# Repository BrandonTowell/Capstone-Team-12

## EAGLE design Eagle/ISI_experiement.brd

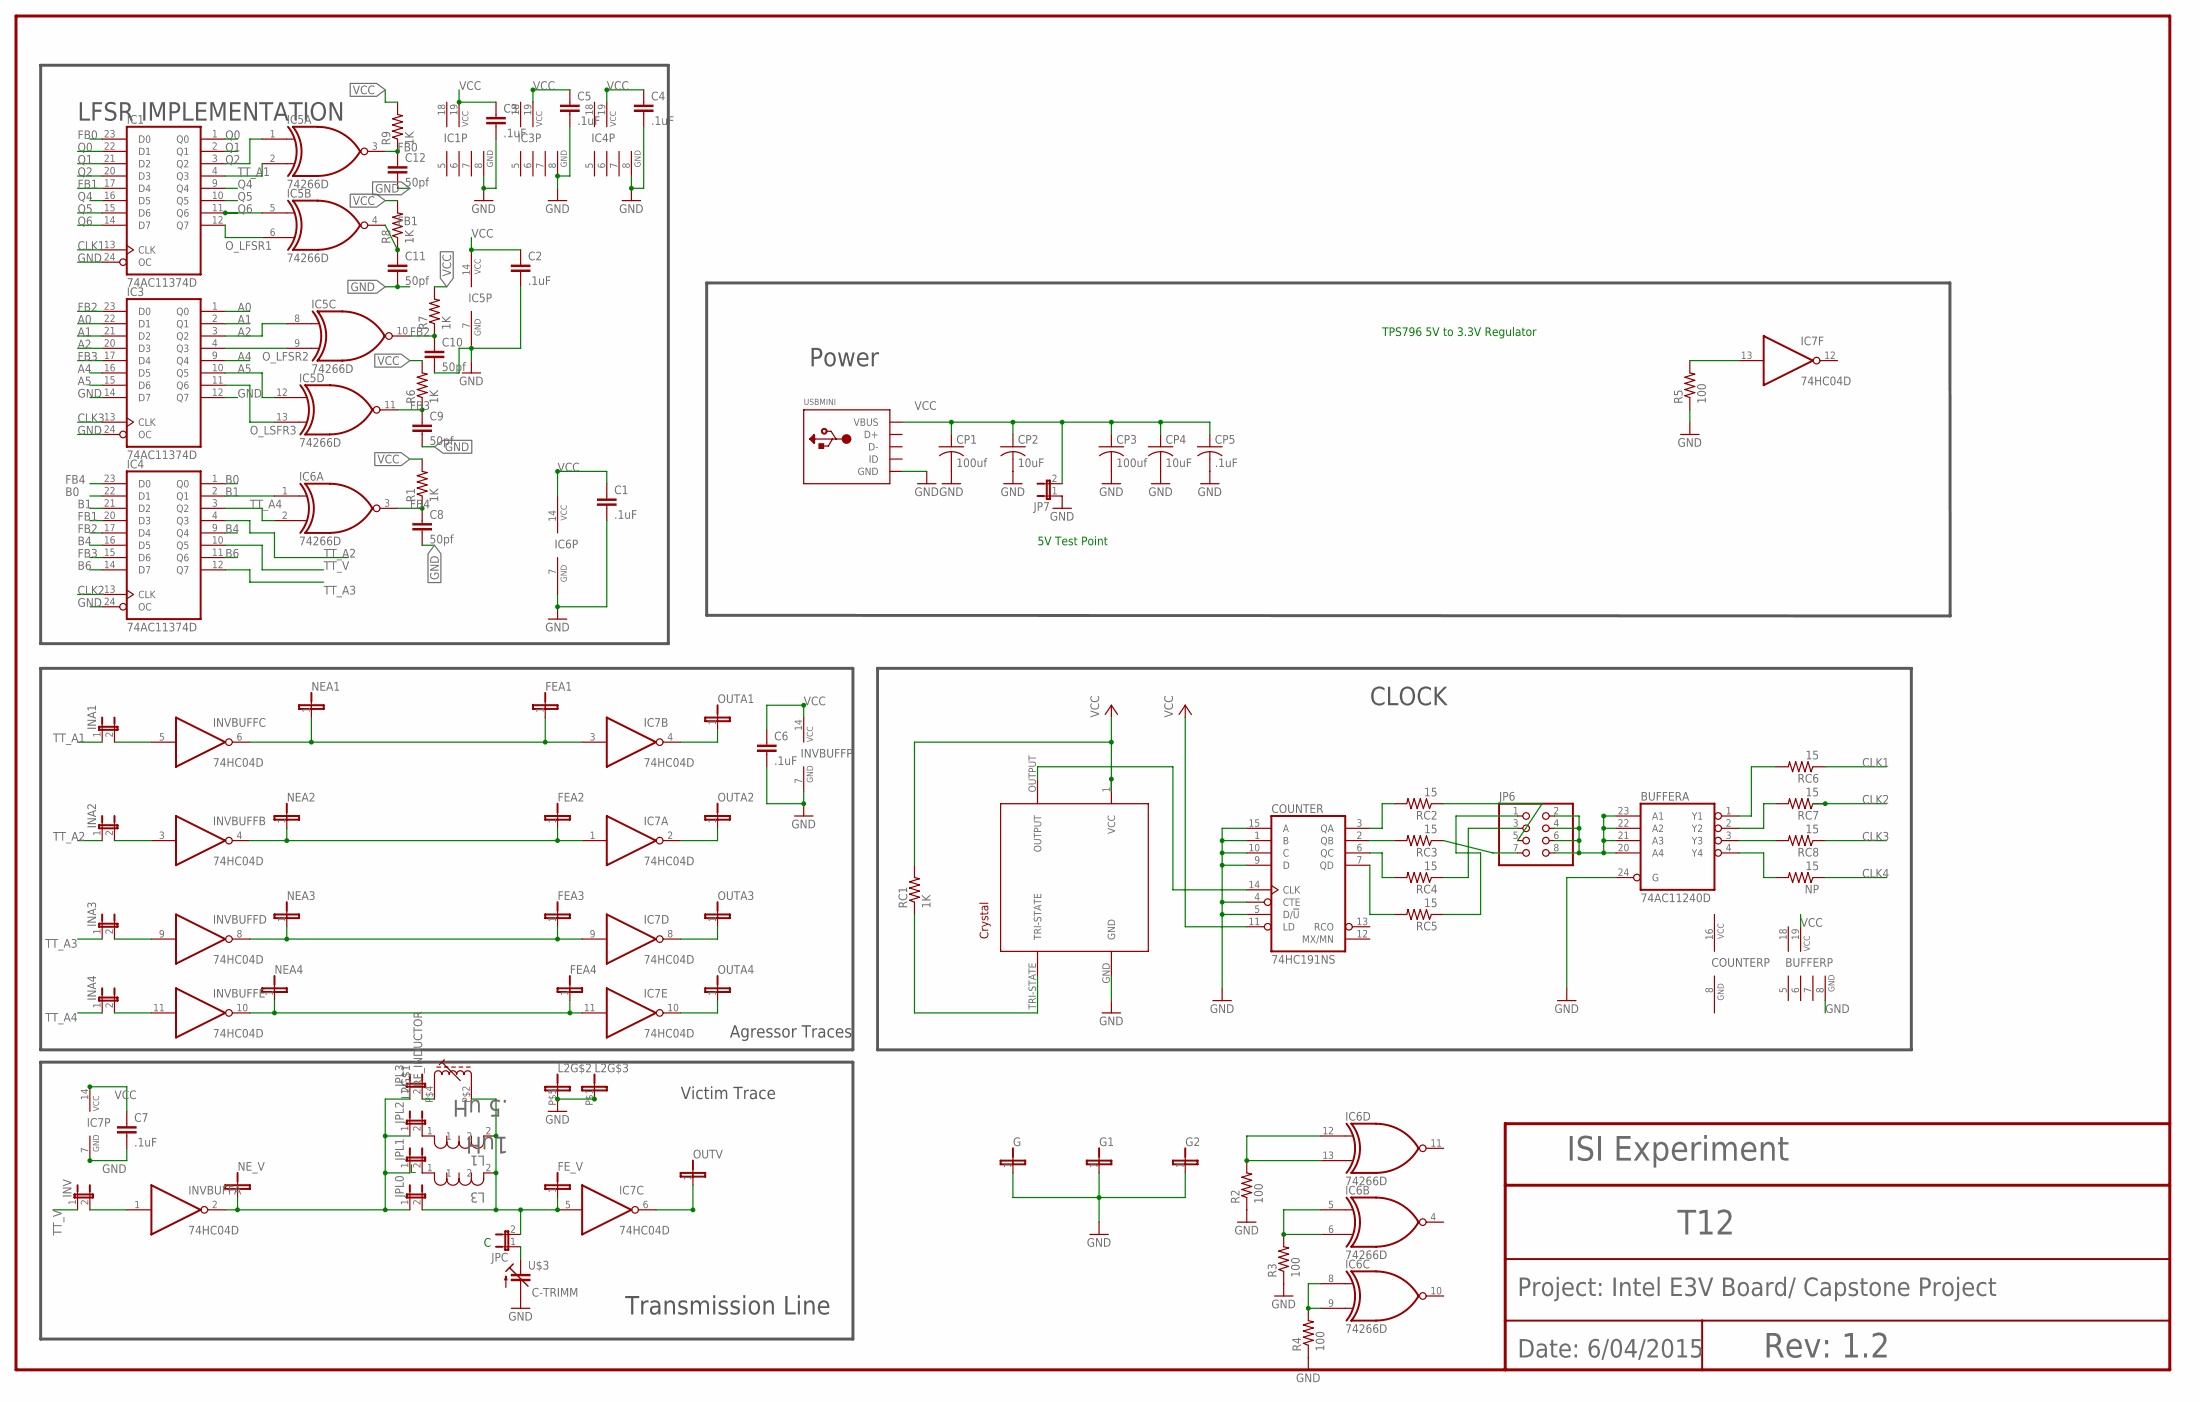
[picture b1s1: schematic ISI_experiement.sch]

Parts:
BUFFER: 74AC11240D; SO24W
C1, C2, C3, C4, C5, C6, C7: .1uF; C0805
C8, C9, C10, C11, C12: 50pf; C0805
COUNTER: 74HC191NS; SO16NS
CP1, CP3: 100uf; C1206K
CP2, CP4: 10uF; C1206K
CP5: .1uF; C1206K
FEA1, FEA2, FEA3, FEA4: JP1
FE_V: JP1
G, G1, G2: JP1
IC1, IC3, IC4: 74AC11374D; SO24W
IC5, IC6: 74266D; SO14
IC7: 74HC04D; SO14
INA1, INA2, INA3, INA4: JP1E; JP1
INV: JP1E; JP1
INVBUFF: 74HC04D; SO14
JP6: PINHD-2X4; 2X04
JP7: JP1E; JP1
JPC: JP1E; JP1
JPL0, JPL1, JPL2, JPL3: JP1E; JP1
L1: .5 uH; INDC2115X15N
L2: RF_INDUCTOR; ADJ_IND_NON_STD_PKG
L3: 1uH; INDC2115X15N
NEA1, NEA2, NEA3, NEA4: JP1
NE_V: JP1
NP: 15; R0805
OUTA1, OUTA2, OUTA3, OUTA4: JP1
OUTV: JP1
R1, R6, R7, R8, R9: 1K; M0805
R2, R3, R4, R5: 100; M0805
RC1: 1K; R0805
RC2, RC3, RC4, RC5, RC6, RC7, RC8: 15; R0805
U$1: ECS-8FX
U$3: C-TRIMM; C_TRIM
USBMINI: USBMINIB; USB-MINIB

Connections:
1: FEA1.1, IC7.3 (I), INVBUFF.6 (O), NEA1.1
2: FEA2.1, IC7.1 (I), INVBUFF.4 (O), NEA2.1
3: FEA3.1, IC7.9 (I), INVBUFF.8 (O), NEA3.1
8: FEA4.1, IC7.11 (I), INVBUFF.10 (O), NEA4.1
A0: IC3.1 (Q0), IC3.22 (D1)
A1: IC3.2 (Q1), IC3.21 (D2)
A2: IC3.3 (Q2), IC3.20 (D3), IC5.8 (I0)
A4: IC3.9 (Q4), IC3.16 (D5)
A5: IC3.10 (Q5), IC3.15 (D6), IC5.12 (I0)
B0: IC4.1 (Q0), IC4.22 (D1)
B1: IC4.2 (Q1), IC4.21 (D2), IC6.1 (I0)
B4: IC4.9 (Q4), IC4.16 (D5)
B6: IC4.11 (Q6), IC4.14 (D7)
CLK1: IC1.13 (CLK), RC6.1
CLK2: IC4.13 (CLK), RC7.1
CLK3: IC3.13 (CLK), RC8.1
CLK4: NP.1
CRY_OUT: COUNTER.14 (CLK), U$1.OUTPUT
FB0: C12.1, IC1.23 (D0), IC5.3 (O), R9.1
FB1: C11.1, IC1.17 (D4), IC4.20 (D3), IC5.4 (O), R8.1
FB2: C10.1, IC3.23 (D0), IC4.17 (D4), IC5.10 (O), R7.1
FB3: C9.1, IC3.17 (D4), IC4.15 (D6), IC5.11 (O), R6.1
FB4: C8.1, IC4.23 (D0), IC6.3 (O), R1.1
GND: BUFFER.5 (GND), BUFFER.6 (GND), BUFFER.7 (GND), BUFFER.8 (GND), BUFFER.24 (G), C1.2, C2.2, C3.2, C4.2, C5.2, C6.2, C7.2, C8.2, C9.2, C10.2, C11.2, C12.2, COUNTER.1 (B), COUNTER.4 (CTE), COUNTER.5 (D/!U), COUNTER.8 (GND), COUNTER.9 (D), COUNTER.10 (C), COUNTER.15 (A), CP1.2, CP2.2, CP3.2, CP4.2, CP5.2, G.1, G1.1, G2.1, IC1.5 (GND), IC1.6 (GND), IC1.7 (GND), IC1.8 (GND), IC1.24 (OC), IC3.5 (GND), IC3.6 (GND), IC3.7 (GND), IC3.8 (GND), IC3.12 (Q7), IC3.14 (D7), IC3.24 (OC), IC4.5 (GND), IC4.6 (GND), IC4.7 (GND), IC4.8 (GND), IC4.24 (OC), IC5.7 (GND), IC6.7 (GND), IC7.7 (GND), INVBUFF.7 (GND), JP7.1, L2.P$1 (1), L2.P$5 (1), R2.1, R3.1, R4.1, R5.1, U$1.GND, U$3.- (G), USBMINI.GND
unnamed: INA2.2, INVBUFF.3 (I)
unnamed: JPL3.2, L2.P$4 (A1)
unnamed: FE_V.1, IC7.5 (I), JPC.2, JPL0.2, L1.2, L2.P$2 (E1), L3.2
unnamed: RC1.1, U$1.TRI-STATE
unnamed: COUNTER.7 (QD), RC5.2
unnamed: JPC.1, U$3.+
unnamed: IC7.4 (O), OUTA1.1
unnamed: INA1.2, INVBUFF.5 (I)
unnamed: COUNTER.3 (QA), RC2.2
unnamed: IC6.12 (I0), IC6.13 (I1), R2.2
unnamed: IC7.6 (O), OUTV.1
unnamed: JPL2.2, L1.1
unnamed: IC7.10 (O), OUTA4.1
unnamed: IC7.2 (O), OUTA2.1
unnamed: INA4.2, INVBUFF.11 (I)
unnamed: INV.2, INVBUFF.1 (I)
unnamed: COUNTER.2 (QB), RC3.2
unnamed: JPL1.2, L3.1
unnamed: INA3.2, INVBUFF.9 (I)
unnamed: COUNTER.6 (QC), RC4.2
unnamed: IC6.5 (I0), IC6.6 (I1), R3.2
unnamed: JP6.5, RC2.1
unnamed: JP6.3, RC4.1
unnamed: JP6.7, RC3.1
unnamed: JP6.1, RC5.1
unnamed: BUFFER.20 (A4), BUFFER.21 (A3), BUFFER.22 (A2), BUFFER.23 (A1), JP6.2, JP6.4, JP6.6, JP6.8
unnamed: BUFFER.1 (Y1), RC6.2
unnamed: BUFFER.2 (Y2), RC7.2
unnamed: BUFFER.3 (Y3), RC8.2
unnamed: BUFFER.4 (Y4), NP.2
unnamed: IC6.8 (I0), IC6.9 (I1), R4.2
unnamed: IC7.13 (I), R5.2
OUTA4: IC7.8 (O), OUTA3.1
O_LFSR1: IC1.12 (Q7), IC5.6 (I1)
O_LFSR2: IC3.4 (Q3), IC5.9 (I1)
O_LSFR3: IC3.11 (Q6), IC5.13 (I1)
Q0: IC1.1 (Q0), IC1.22 (D1)
Q1: IC1.2 (Q1), IC1.21 (D2)
Q2: IC1.3 (Q2), IC1.20 (D3), IC5.1 (I0)
Q4: IC1.9 (Q4), IC1.16 (D5)
Q5: IC1.10 (Q5), IC1.15 (D6)
Q6: IC1.11 (Q6), IC1.14 (D7), IC5.5 (I0)
TT_A1: IC1.4 (Q3), IC5.2 (I1), INA1.1
TT_A2: IC4.4 (Q3), INA2.1
TT_A3: IC4.12 (Q7), INA3.1
TT_A4: IC4.3 (Q2), IC6.2 (I1), INA4.1
TT_V: IC4.10 (Q5), INV.1
V1: INVBUFF.2 (O), JPL0.1, JPL1.1, JPL2.1, JPL3.1, NE_V.1
VCC: BUFFER.18 (VCC), BUFFER.19 (VCC), C1.1, C2.1, C3.1, C4.1, C5.1, C6.1, C7.1, COUNTER.11 (LD), COUNTER.16 (VCC), CP1.1, CP2.1, CP3.1, CP4.1, CP5.1, IC1.18 (VCC), IC1.19 (VCC), IC3.18 (VCC), IC3.19 (VCC), IC4.18 (VCC), IC4.19 (VCC), IC5.14 (VCC), IC6.14 (VCC), IC7.14 (VCC), INVBUFF.14 (VCC), JP7.2, R1.2, R6.2, R7.2, R8.2, R9.2, RC1.2, U$1.1 (VCC), USBMINI.VBUS

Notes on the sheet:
LFSR IMPLEMENTATION
Transmission Line
Power
CLOCK
ISI Experiment
T12
Rev: 1.2
Date: 6/04/2015
Project: Intel E3V Board/ Capstone Project
TPS796 5V to 3.3V Regulator
5V Test Point
Victim Trace
Agressor Traces

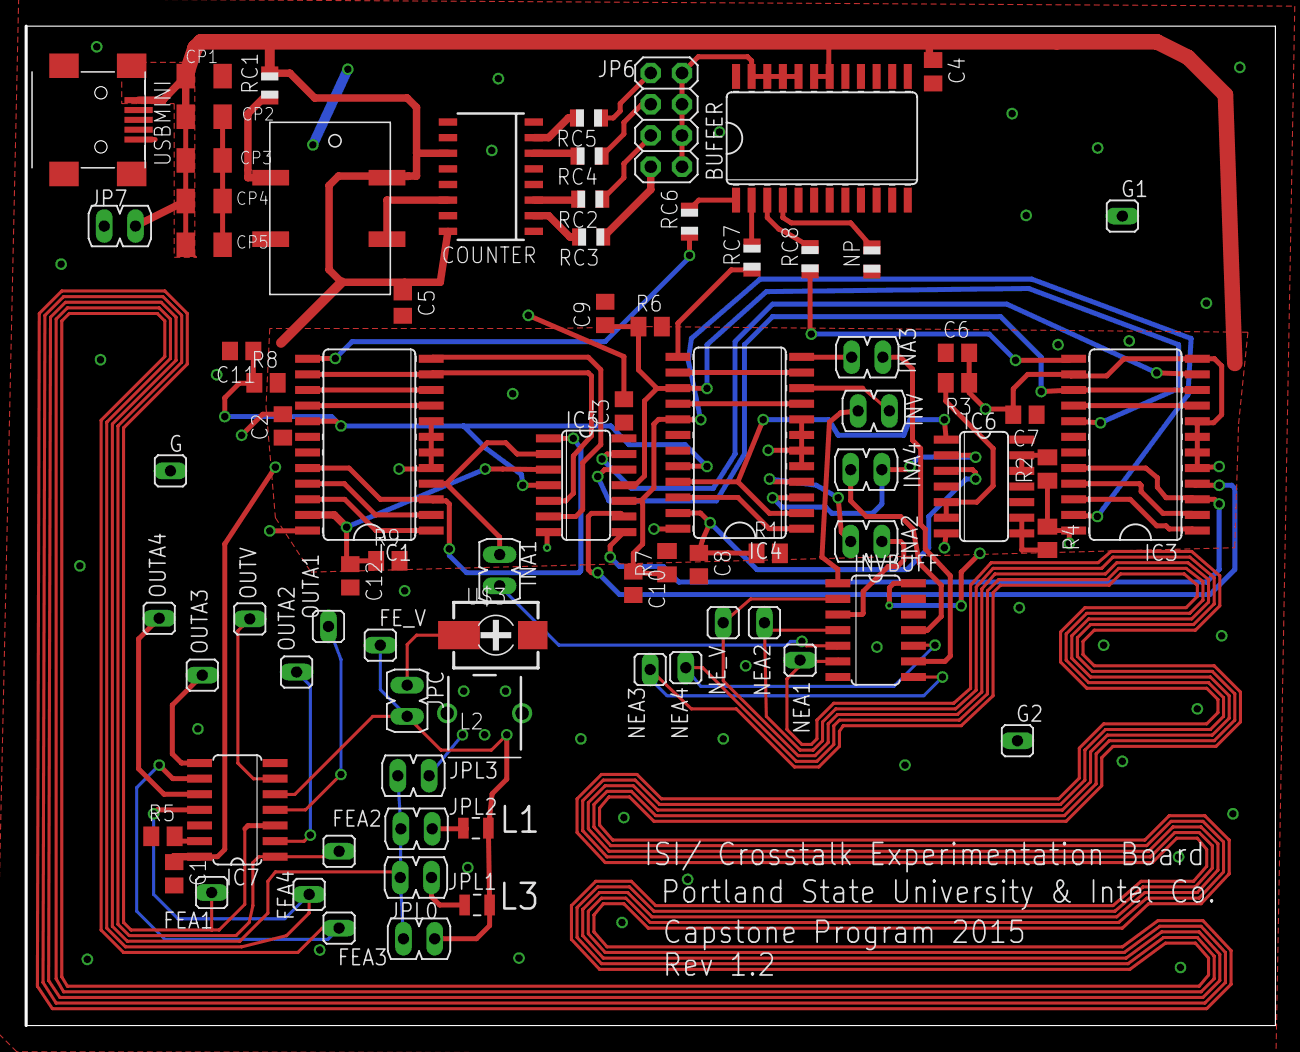
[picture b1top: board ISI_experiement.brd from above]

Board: 2 copper layers, 101.6 x 81.3 mm, 80 parts (0 on the bottom side), 72 nets.

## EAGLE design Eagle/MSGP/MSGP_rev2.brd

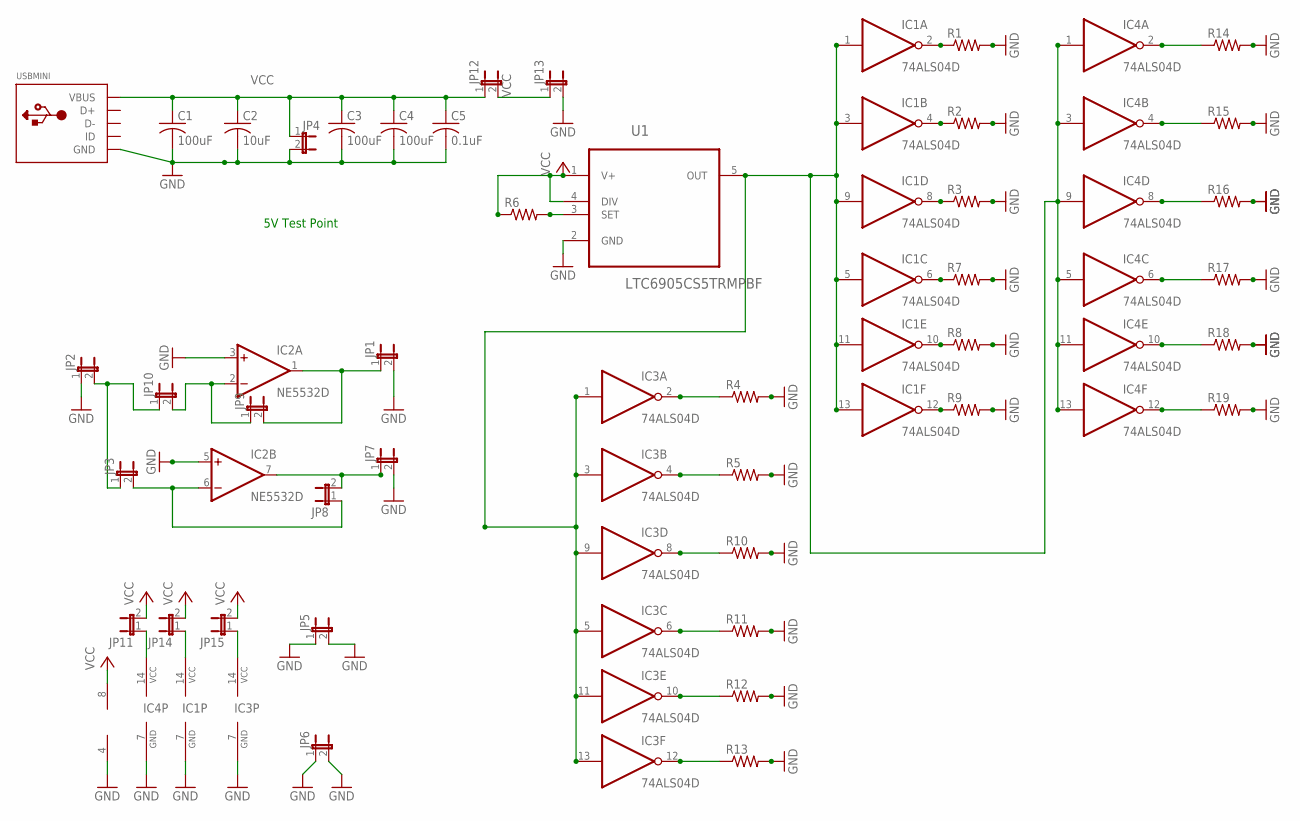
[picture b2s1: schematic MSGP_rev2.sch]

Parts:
C1, C3, C4: 100uF; C1206K
C2: 10uF; C1206K
C5: 0.1uF; C1206K
IC1, IC3, IC4: 74ALS04D; SO14
IC2: NE5532D; SO08
JP1, JP2, JP3, JP4, JP5, JP6, JP7, JP8, JP9, JP10, JP11, JP12, JP13, JP14, JP15: JP1E; JP1
R1, R2, R3, R4, R5, R6, R7, R8, R9, R10, R11, R12, R13, R14, R15, R16, R17, R18, R19: R-US_0204/2V; 0204V
U1: LTC6905CS5TRMPBF; SOT95P280X100-5N
USBMINI: USBMINIB; USB-MINIB

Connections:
GNDA: C1.2, C2.2, C3.2, C4.2, C5.2, IC2.3 (+IN), IC2.4 (V-), IC2.5 (+IN), JP1.2, JP2.1, JP4.2, JP5.2, JP6.2, JP7.2, JP13.2, USBMINI.GND
GND_D: IC1.7 (GND), IC3.7 (GND), IC4.7 (GND), JP5.1, JP6.1, R1.2, R2.2, R3.2, R4.2, R5.2, R7.2, R8.2, R9.2, R10.2, R11.2, R12.2, R13.2, R14.2, R15.2, R16.2, R17.2, R18.2, R19.2, U1.2 (GND)
unnamed: IC1.1 (I), IC1.3 (I), IC1.5 (I), IC1.9 (I), IC1.11 (I), IC1.13 (I), IC3.1 (I), IC3.3 (I), IC3.5 (I), IC3.9 (I), IC3.11 (I), IC3.13 (I), IC4.1 (I), IC4.3 (I), IC4.5 (I), IC4.9 (I), IC4.11 (I), IC4.13 (I), U1.5 (OUT)
unnamed: IC2.6 (-IN), JP3.2, JP8.1
unnamed: IC2.1 (OUT), JP1.1, JP9.2
unnamed: IC1.10 (O), R8.1
unnamed: IC2.2 (-IN), JP9.1, JP10.2
unnamed: R6.2, U1.3 (SET)
unnamed: IC1.2 (O), R1.1
unnamed: IC1.4 (O), R2.1
unnamed: IC1.8 (O), R3.1
unnamed: IC1.6 (O), R7.1
unnamed: IC1.12 (O), R9.1
unnamed: IC2.7 (OUT), JP7.1, JP8.2
unnamed: IC3.10 (O), R12.1
unnamed: IC4.14 (VCC), JP11.1
unnamed: IC3.2 (O), R4.1
unnamed: IC3.4 (O), R5.1
unnamed: IC3.8 (O), R10.1
unnamed: IC3.6 (O), R11.1
unnamed: IC3.12 (O), R13.1
unnamed: IC4.10 (O), R18.1
unnamed: IC1.14 (VCC), JP14.1
unnamed: IC4.2 (O), R14.1
unnamed: IC4.4 (O), R15.1
unnamed: IC4.8 (O), R16.1
unnamed: IC4.6 (O), R17.1
unnamed: IC4.12 (O), R19.1
unnamed: IC3.14 (VCC), JP15.1
unnamed: JP2.2, JP3.1, JP10.1
VCC: C1.1, C2.1, C3.1, C4.1, C5.1, IC2.8 (V+), JP4.1, JP11.2, JP12.1, JP12.2, JP13.1, JP14.2, JP15.2, R6.1, U1.1 (V+), U1.4 (DIV), USBMINI.VBUS

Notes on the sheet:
5V Test Point

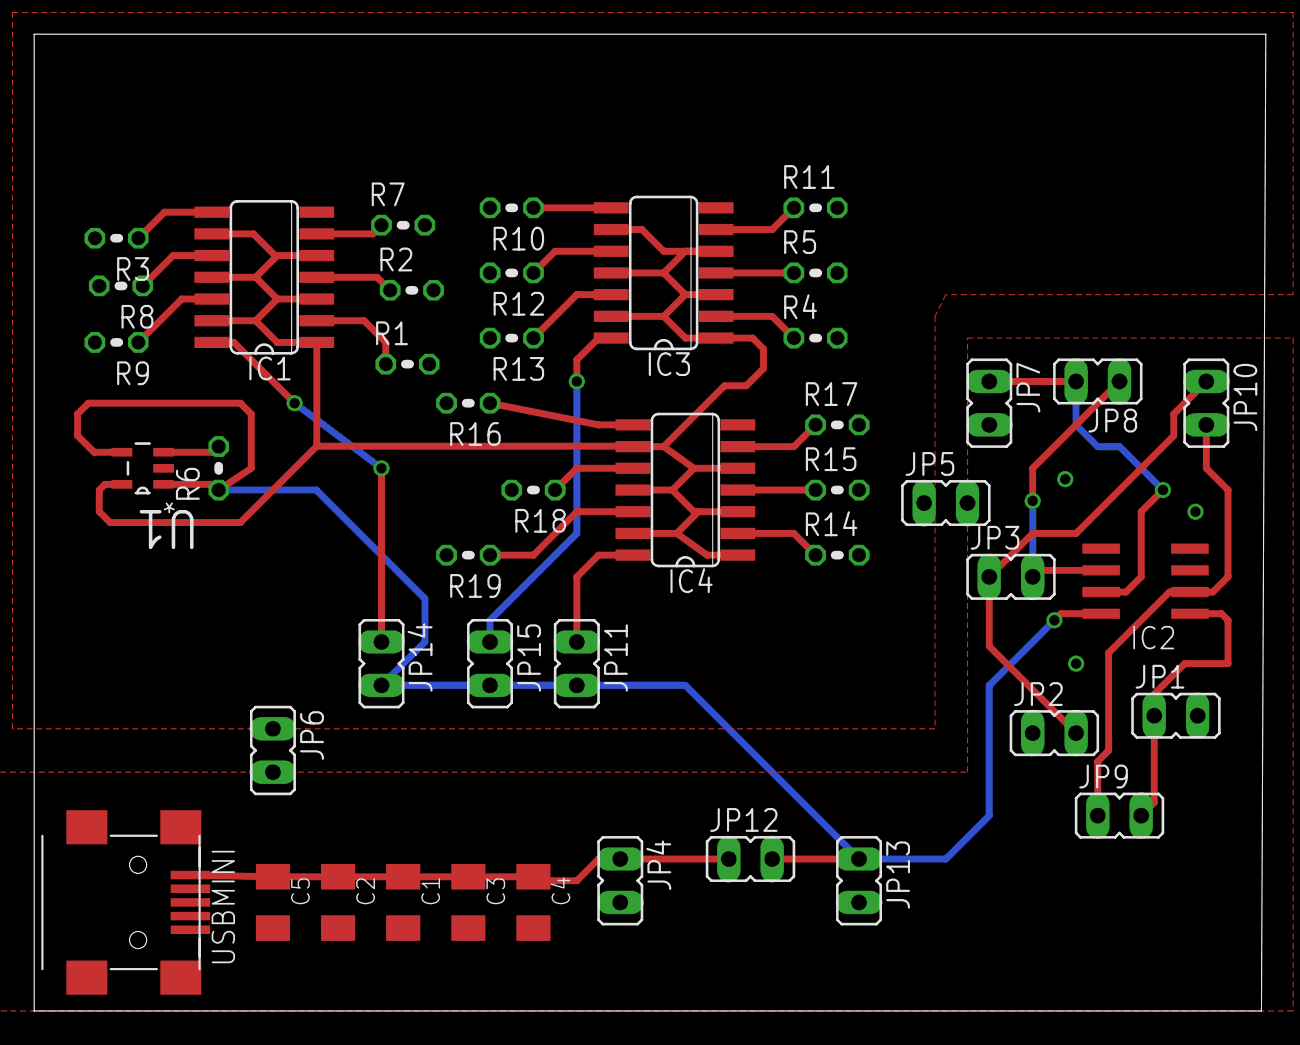
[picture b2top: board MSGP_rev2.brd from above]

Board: 2 copper layers, 72.1 x 57.1 mm, 45 parts (0 on the bottom side), 31 nets.

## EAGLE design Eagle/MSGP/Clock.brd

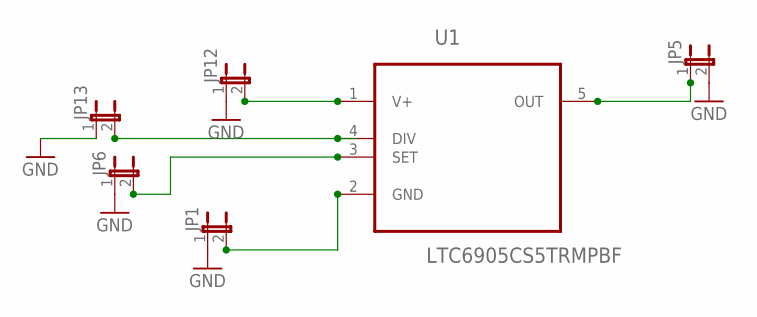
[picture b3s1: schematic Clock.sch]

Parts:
JP1, JP5, JP6, JP12, JP13: JP1E; JP1
U1: LTC6905CS5TRMPBF; SOT95P280X100-5N

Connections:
GND: JP1.1, JP5.2, JP6.1, JP12.1, JP13.1
unnamed: JP12.2, U1.1 (V+)
unnamed: JP13.2, U1.4 (DIV)
unnamed: JP6.2, U1.3 (SET)
unnamed: JP1.2, U1.2 (GND)
unnamed: JP5.1, U1.5 (OUT)

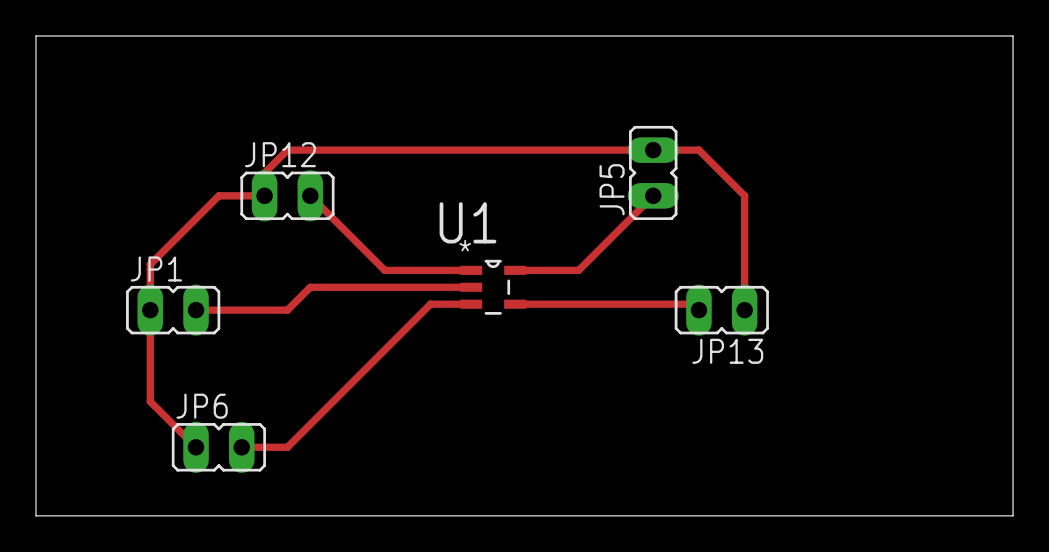
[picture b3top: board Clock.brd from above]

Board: 2 copper layers, 54.3 x 26.7 mm, 6 parts (0 on the bottom side), 6 nets.

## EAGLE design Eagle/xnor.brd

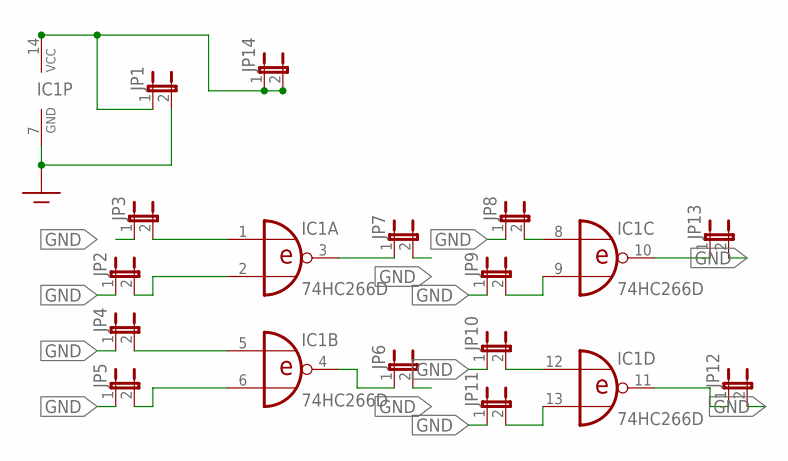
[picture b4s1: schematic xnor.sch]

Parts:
IC1: 74HC266D; SO14
JP1, JP2, JP3, JP4, JP5, JP6, JP7, JP8, JP9, JP10, JP11, JP12, JP13, JP14: JP1E; JP1

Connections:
GND: IC1.7 (GND), JP1.2, JP2.1, JP3.1, JP4.1, JP5.1, JP6.2, JP7.2, JP8.1, JP9.1, JP10.1, JP11.1, JP12.2, JP13.2
unnamed: IC1.10 (O), JP13.1
unnamed: IC1.1 (I0), JP3.2
unnamed: IC1.2 (I1), JP2.2
unnamed: IC1.5 (I0), JP4.2
unnamed: IC1.6 (I1), JP5.2
unnamed: IC1.4 (O), JP6.1
unnamed: IC1.3 (O), JP7.1
unnamed: IC1.8 (I0), JP8.2
unnamed: IC1.9 (I1), JP9.2
unnamed: IC1.12 (I0), JP10.2
unnamed: IC1.13 (I1), JP11.2
unnamed: IC1.11 (O), JP12.1
VCC: IC1.14 (VCC), JP1.1, JP14.1, JP14.2

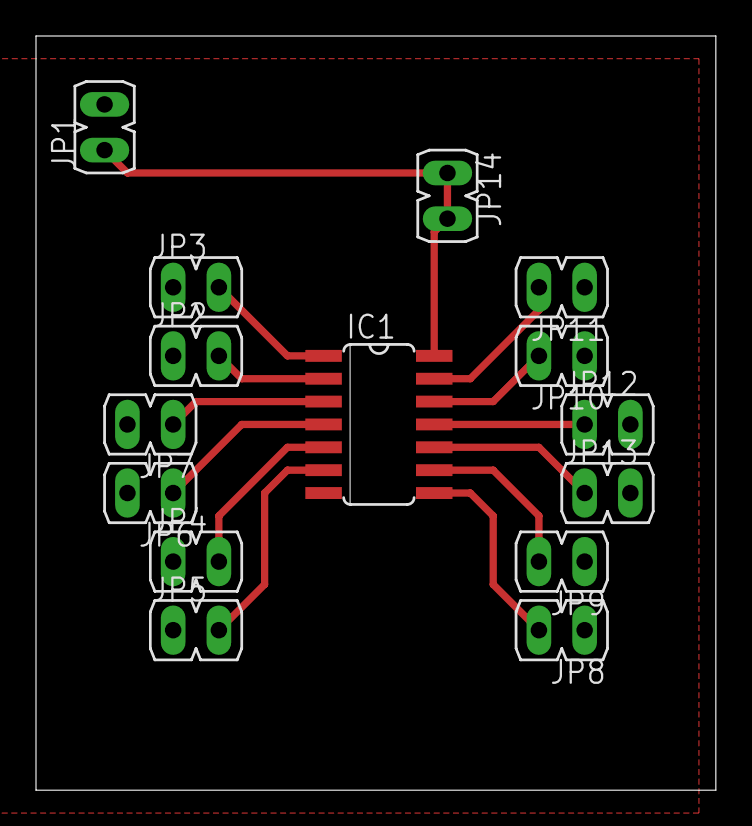
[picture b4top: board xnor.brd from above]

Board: 2 copper layers, 37.8 x 41.9 mm, 15 parts (0 on the bottom side), 14 nets.

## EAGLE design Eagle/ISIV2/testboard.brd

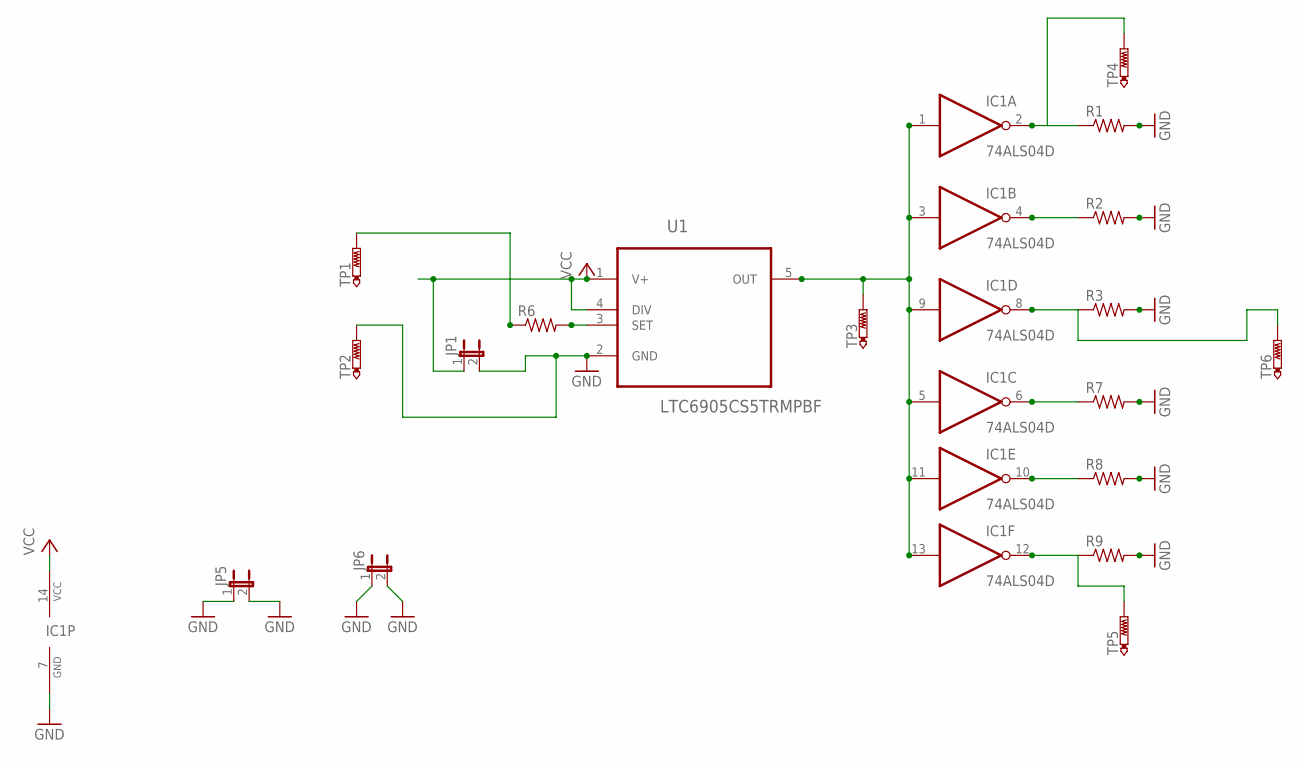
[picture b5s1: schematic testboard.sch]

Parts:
IC1: 74ALS04D; SO14
JP1, JP5, JP6: JP1E; JP1
R1, R2, R3, R6, R7, R8, R9: R-US_0204/2V; 0204V
TP1, TP2, TP3, TP4, TP5, TP6: PTR1B2,54; B2,54
U1: LTC6905CS5TRMPBF; SOT95P280X100-5N

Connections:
GND: IC1.7 (GND), JP1.2, JP5.1, JP5.2, JP6.1, JP6.2, R1.2, R2.2, R3.2, R7.2, R8.2, R9.2, TP2.TP, U1.2 (GND)
unnamed: IC1.1 (I), IC1.3 (I), IC1.5 (I), IC1.9 (I), IC1.11 (I), IC1.13 (I), TP3.TP, U1.5 (OUT)
unnamed: IC1.10 (O), R8.1
unnamed: R6.2, U1.3 (SET)
unnamed: IC1.2 (O), R1.1, TP4.TP
unnamed: IC1.4 (O), R2.1
unnamed: IC1.8 (O), R3.1, TP6.TP
unnamed: IC1.6 (O), R7.1
unnamed: IC1.12 (O), R9.1, TP5.TP
VCC: IC1.14 (VCC), JP1.1, R6.1, TP1.TP, U1.1 (V+), U1.4 (DIV)

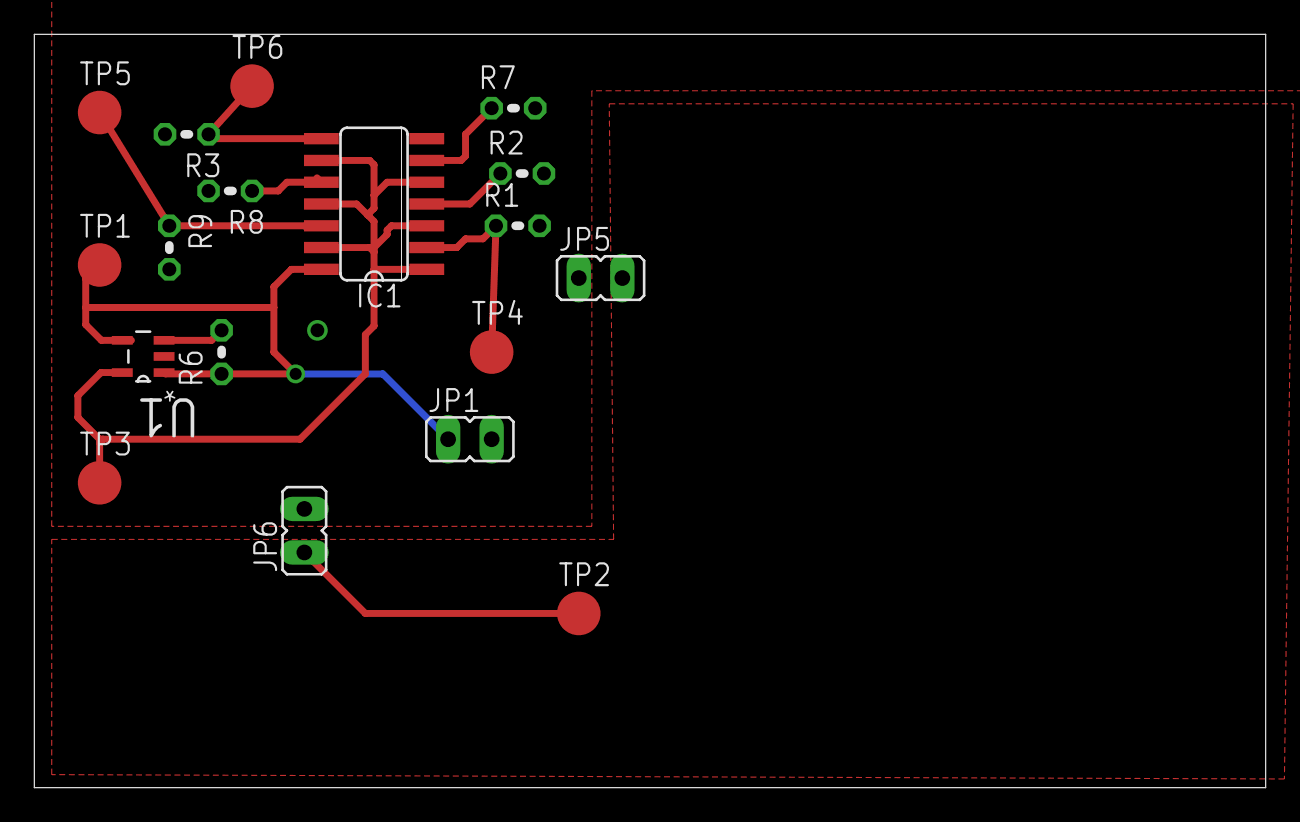
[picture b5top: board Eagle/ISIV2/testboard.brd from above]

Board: 2 copper layers, 71.8 x 43.9 mm, 18 parts (0 on the bottom side), 10 nets.

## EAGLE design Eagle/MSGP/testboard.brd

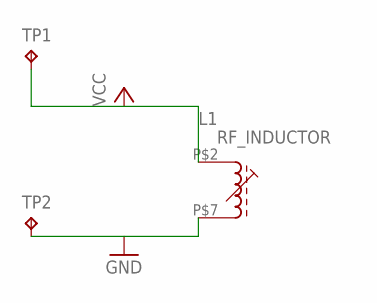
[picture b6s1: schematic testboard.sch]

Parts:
L1: RF_INDUCTOR; ADJ_IND_NON_STD_PKG
TP1, TP2: TPB2,54; B2,54

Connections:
GND: L1.P$7 (E1), TP2.TP
VCC: L1.P$2 (A1), TP1.TP

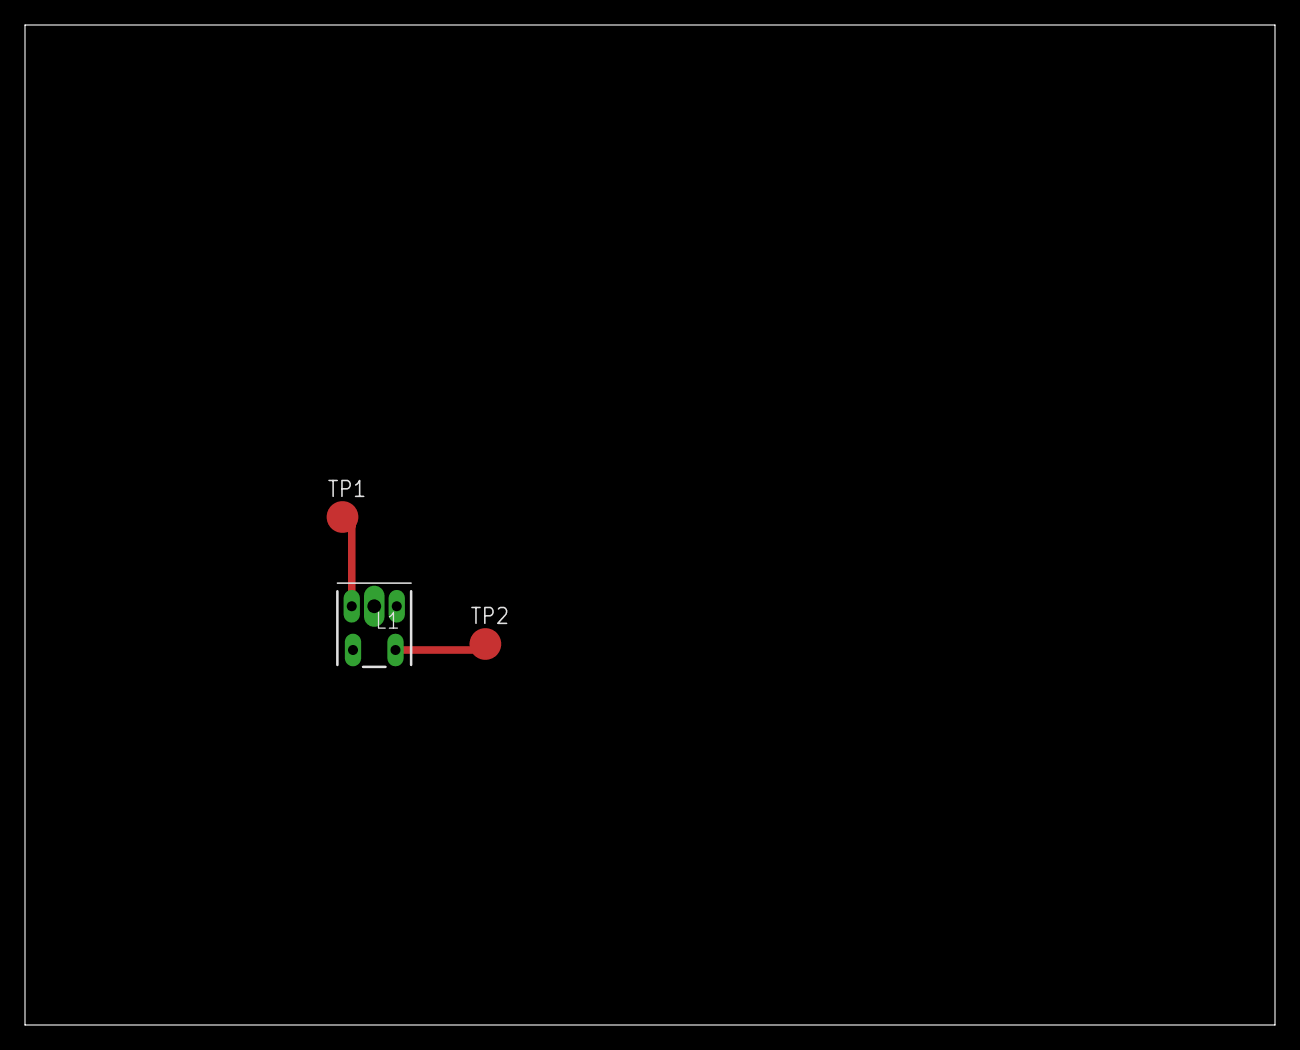
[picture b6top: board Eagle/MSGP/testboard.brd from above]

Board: 2 copper layers, 100.0 x 80.0 mm, 3 parts (0 on the bottom side), 2 nets.

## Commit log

2015-03-07 ISI experiment
    Test upload
2015-03-07 Team Eval
    Evaluations form is added for group members to complete and turn in to
    Morris ASAP and again at the end of the term.
2015-03-07 WPR added
2015-03-07 WPRs
    Uploaded WPR file from Google Document Repo To GitHub Repo
2015-03-07 Revert "WPR added"
    This reverts commit bc3c9c03f2d13f4134c4ff27759bec9a1126dc3d.
2015-03-07 Added Archive documentation
2015-03-07 Current Documentation
2015-03-07 uploaded PDS PDF
2015-03-07 Updated Naming Convention
2015-03-07 deleted PDS PDF
    will not open on screen, makes no difference
2015-03-07 Uploaded WPR
2015-03-07 Project Proposal 1.5
    Added Project Proposal 1.5 moved 1.4 to archive folder
2015-03-07 Renaming
2015-03-07 my wprs and original project description
2015-03-07 Updated Project Proposal
2015-03-08 New Project Gantt Chart
    Also WPR
2015-03-10 add it WPR and schematic
2015-03-12 changed flip-flop
    changed flip flop to ordered part, original part was not available at
    DigiKey
2015-03-12 Added Research Folder
    Added research folder and added research papers for mixed signal devices
2015-03-14 WPR and Connector description
2015-03-14 Project Proposal
2015-03-14 ISI Description
2015-03-14 Proposal Update
2015-03-14 Cleanup
2015-03-14 BOM and WPR
2015-03-14 Split subtotals
2015-03-14 Project Proposal Archived
2015-03-14 Renamed Project Proposal
2015-03-14 WPR Update
2015-03-14 Renamed Project Schedule
2015-03-14 Updated formatting
    Changed looked and feel on Requirements Documents and changed date on
    Proposal.
2015-03-15 Updated
    Table of contents and documentation
2015-03-15 Updated Table of contents and Links
2015-03-16 WPR
    WPR and some progress LSFR pattern generation for crosstalk aspect of
    the experiment.
2015-03-22 ISI Description Draft
    Has a brief description and a list of requirements to eventually be
    added to PDS
2015-03-22 ignore just clean up
    Moved some files into correct folder and deleted some saved buffers
2015-03-23 Luis WPR
    3-22 WPR
2015-03-25 Updated Procedure
2015-03-25 WPR/BLKDIAGRAM/DetailedReqs
2015-03-25 Naming update
2015-03-25 Uploading ISI Doc
2015-03-25 Edited Documents
2015-03-25 Project Schedule
2015-03-25 Renamed Project Sched
2015-03-25 Kris added WPR
2015-03-27 ISI part library
    Started part library with schematic and parts both on mm to match what
    Kris wanted
2015-03-29 added items to library
    added single pin header and inverted buffer
2015-03-30 minor changes
    added some parts and ensure parts were worked on both schematic and
    board.
2015-04-01 Update to docs
    Updated BOM and added goal to ISI experiment description
2015-04-01 Small format changes
    merged formating so all documents have the same feel
2015-04-01 Created Connector Reliability
2015-04-01 Deleted file
2015-04-01 Updated BLock Diagram
2015-04-01 ISI edits
    added travis correction and equipment
2015-04-01 WPR upload
2015-04-01 Added WPR folder and WPR
2015-04-01 Updated Connector document
2015-04-01 Schedule Update
2015-04-01 some of Faust suggestions
    I like schedule v3.
2015-04-02 WPR Uploaded
2015-04-02 schematic for power supply
2015-04-03 merge power
    needs more work just uploaded to save progress
2015-04-03 for got this
2015-04-04 added aggressor and LFSR
    need to add a clock and review a inductor part and schematic
2015-04-04 made space for clock
2015-04-04 clk sch
2015-04-04 MSGP sch
2015-04-05 Update Schematic
2015-04-05 wrong file uploaded
2015-04-05 MSBP board
2015-04-05 add f_type for brandon
2015-04-05 WPR Folder
2015-04-05 added Kris WPR
2015-04-05 new MSGP
2015-04-05 added clock to ISI
    clock and labels added and some minor appearance changes
2015-04-05 WPR
    current week WPR
2015-04-06 Updated Schedule
2015-04-06 really close to final ISI
    missing inductor package dimensions and one cap value.
2015-04-06 Document
2015-04-09 Updated ISI schematic and board
2015-04-10 ISI updated
    Still need to make 2 parts but that should no affect routing of LFSR.
2015-04-12 Update Eagle Schematic
2015-04-12 WPR
    Created WPR folder and uploaded WPR for 04_12
2015-04-12 Added WPR
2015-04-12 library
2015-04-12 just library
2015-04-12 MSGP board
    placed but not route
2015-04-12 MSGP schematic
2015-04-15 Schematic/Layout Update
2015-04-15 fixed polygon
    Because Eagle is dumb….
2015-04-16 first run full layout of isi board
2015-04-17 upload latest isi board
2015-04-18 MSG layout
2015-04-18 added wpr and berbers for msg experiment
2015-04-20 some changes to the traces
2015-04-21 WPRS
2015-04-21 ISI with test points
    added test point to near and far end of TL
2015-04-23 Schem
2015-04-23 Updated Schematic
2015-04-26 test board included
2015-04-26 test board
    debug board
2015-04-30 version sent to oshpark
2015-04-30 WPRs and Test Board
    Test board layout
2015-05-10 some clean up
2015-05-11 WPR folders
2015-05-21 late update
2015-05-25 changes to git
2015-05-25 Poster/WPRS
    Update
2015-05-26 poster
2015-05-27 minor poster update
2015-05-27 Poster Final?
2015-05-27 last change to poster
2015-05-27 Poster PDF
2015-06-07 Updates to Layout/Schem
2015-06-09 updated boards
    fixed some of the issued we encountered while making the board
2015-06-10 FINAL REPORT ROUGH
2015-06-10 minor changes to MSGP rev2
    change one trace to digital ground
2015-06-10 Revert "FINAL REPORT ROUGH"
    This reverts commit 7f0f0384c8b78845eb1ecfbf6d1b26aa7f46bb10.
2015-06-10 Revert "Revert "FINAL REPORT ROUGH""
    This reverts commit 0e6b22150cd65c9db7fe457fae2aab53b9e0f6cc.
2015-06-10 Presentation/Passdown
2015-06-10 Pres/Passdown
2015-06-10 draft of pass down ISI
    missing summary
2015-06-10 Pass down has a summary
    to be honest just copied from the detailed description
2015-06-10 Presentation
2015-06-10 BOM updated
2015-06-10 LFSR code
    code added in vertigo and PDF for easy reading
2015-06-10 updated MSGP
    added clock, opamp and resistor cost
2015-06-11 some changes to report
    added BOM and code
2015-06-11 Report
2015-06-11 Report upload
2015-06-11 late additions
    ISI additions
2015-06-12 table of content done
